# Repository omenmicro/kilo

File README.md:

# OMEN KILO

As-easy-as-possible, but still expandable single board computer with 6809 / 6309 CPU.

[Essential ICs on AliExpress](https://alitronik.com/omen-kilo-pack/)
[Essential ICs on eBay](https://alitronik.com/omen-kilo-pack-ebay/)

_Great thank to the [Svejda - Goldmann](https://svejda-goldmann.cz/) for the great OMEN artworks_

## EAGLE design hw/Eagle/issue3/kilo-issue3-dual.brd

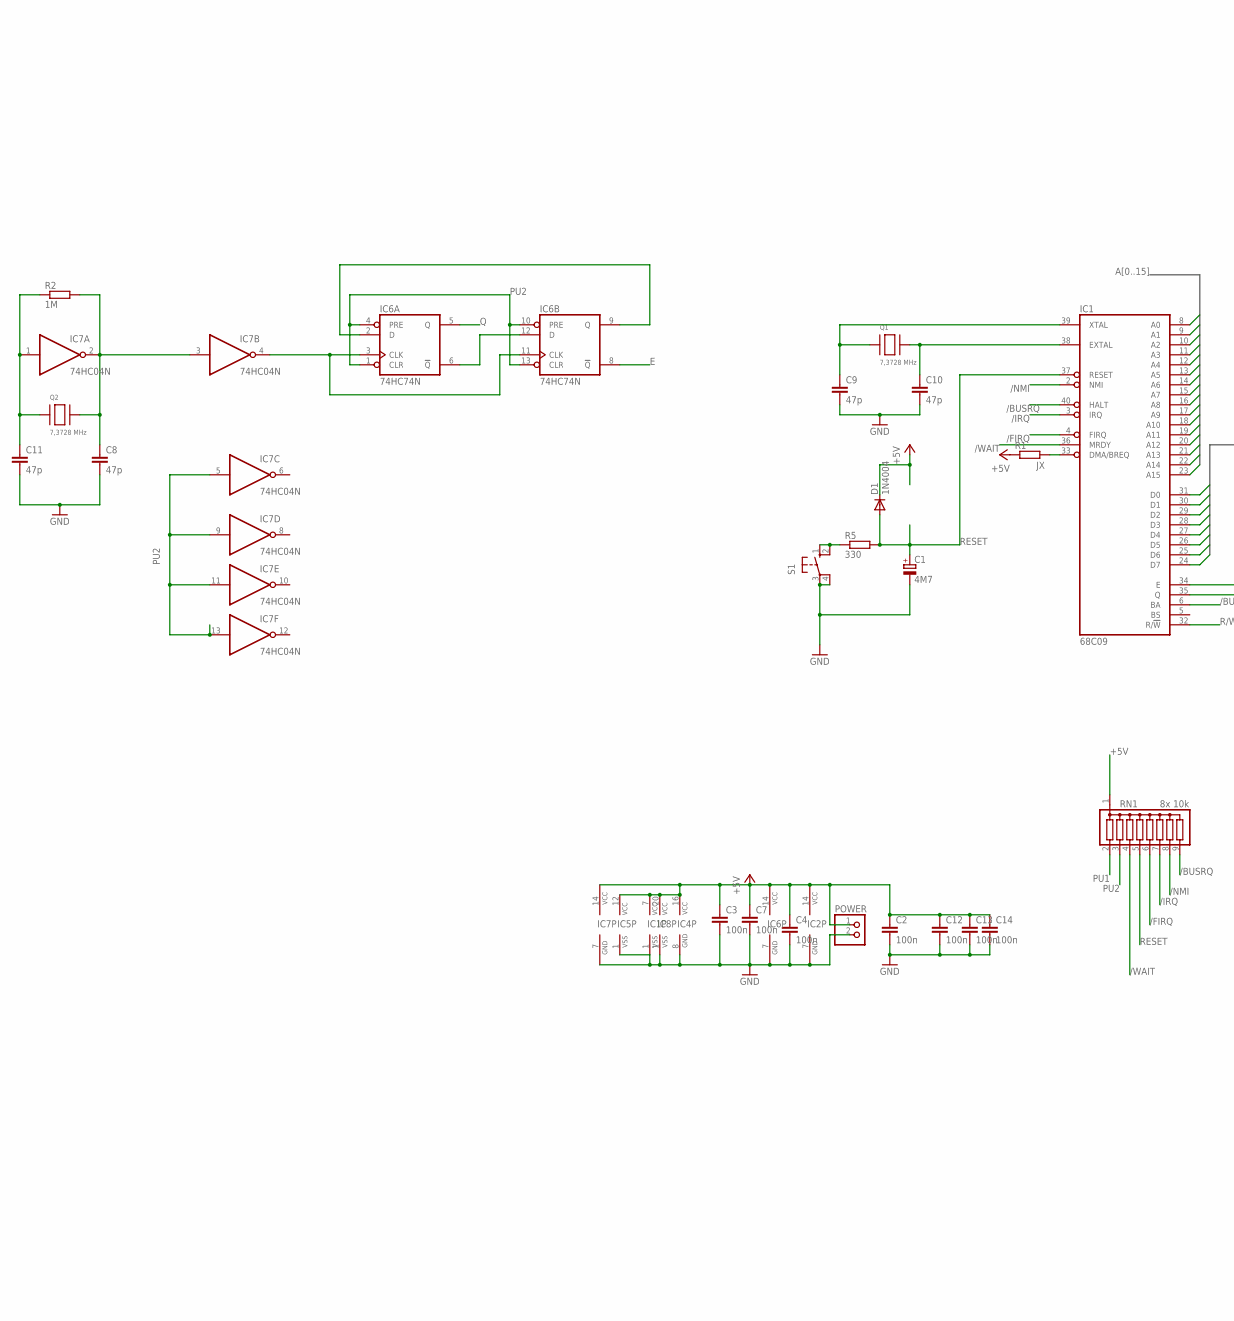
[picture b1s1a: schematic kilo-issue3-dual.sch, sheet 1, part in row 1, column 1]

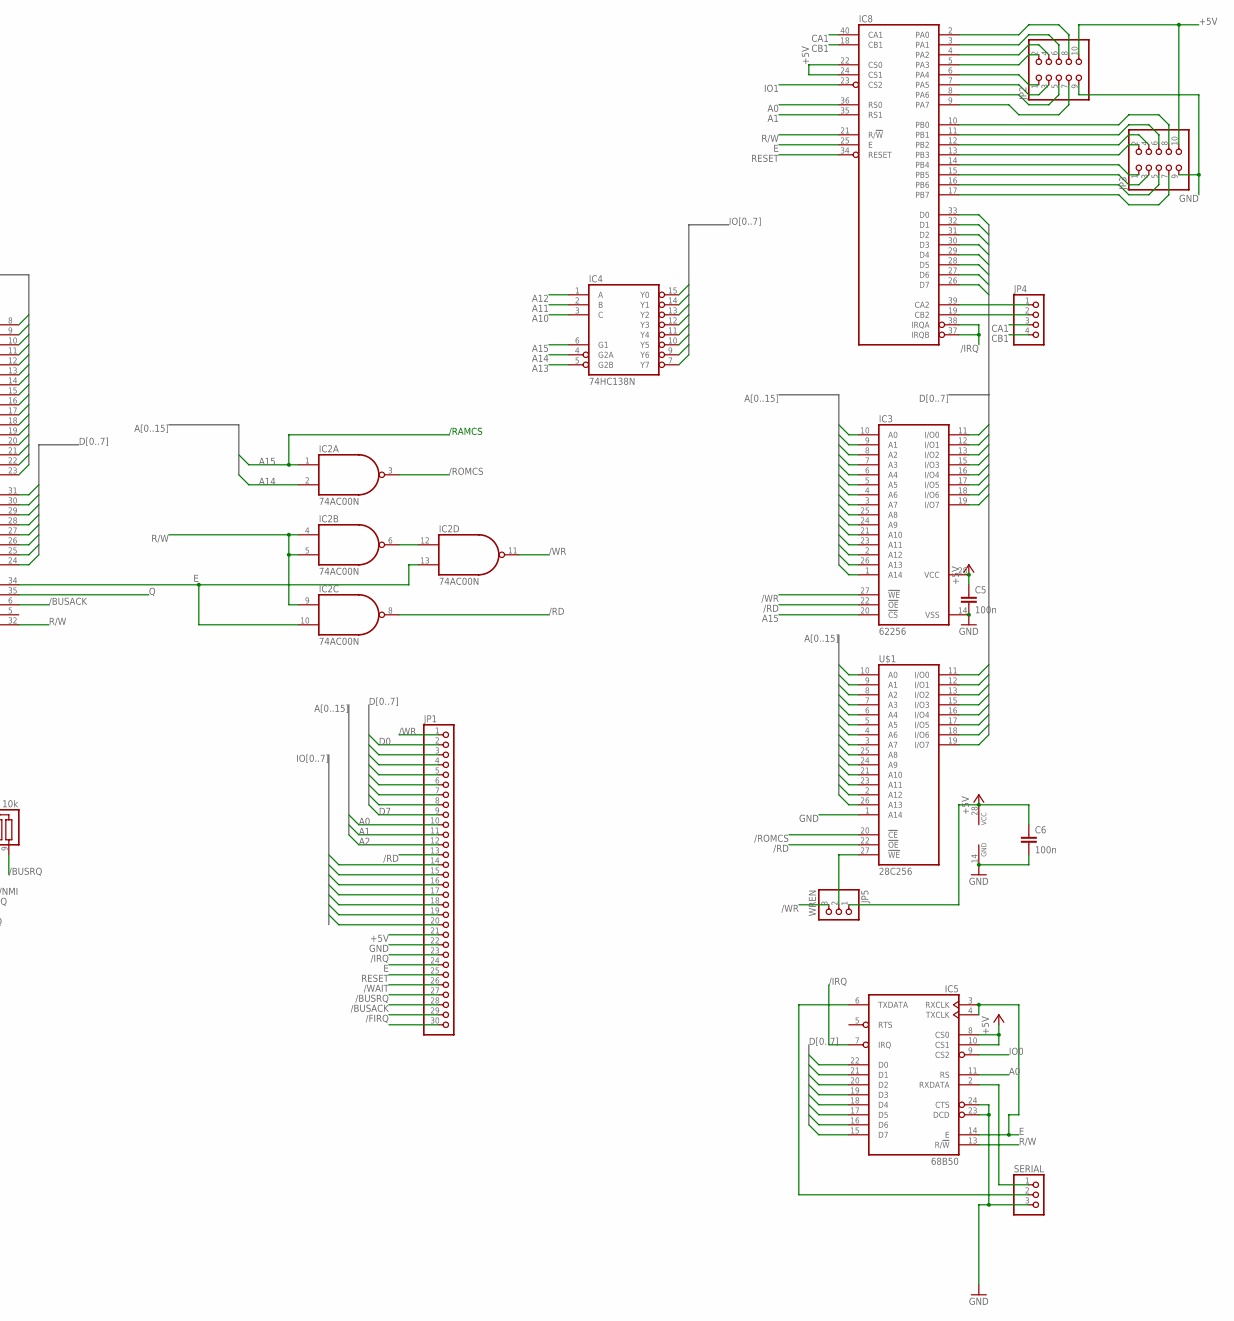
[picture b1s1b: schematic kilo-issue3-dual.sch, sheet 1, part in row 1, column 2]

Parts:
C1: 4M7; E2,5-6
C2, C3, C4, C5, C6, C7, C12, C13, C14: 100n; C025-030X050
C8, C9, C10, C11: 47p; C025-030X050
D1: 1N4004; DO41-10
IC1: 68C09; DIL40
IC2: 74AC00N; DIL14
IC3: 62256; DIL28-6
IC4: 74HC138N; DIL16
IC5: 68B50; DIL24
IC6: 74HC74N; DIL14
IC7: 74HC04N; DIL14
IC8: 6821; DIL40
JP1: PINHD-1X30; 1X30
JP2, JP3: PINHD-2X5; 2X05
JP4: PINHD-1X4; 1X04
JP5: WREN; 1X03
POWER: PINHD-1X2; 1X02
Q1, Q2: 7,3728 MHz; HC49US
R1: JX; M0805
R2: 1M; 0207/7
R5: 330; 0207/7
RN1: 8x 10k; SIL9
S1: 40-XX; B3F-40XX
SERIAL: PINHD-1X3; 1X03
U$1: 28C256; DIL28

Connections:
+5V: C2.1, C3.1, C4.1, C5.1, C6.1, C7.1, C12.1, C13.1, C14.1, D1.C, IC1.7 (VCC), IC2.14 (VCC), IC3.28 (VCC), IC4.16 (VCC), IC5.8 (CS0), IC5.10 (CS1), IC5.12 (VCC), IC6.14 (VCC), IC7.14 (VCC), IC8.20 (VCC), IC8.22 (CS0), IC8.24 (CS1), JP1.21, JP2.10, JP3.10, JP5.1, POWER.1, R1.1, RN1.1, U$1.28 (VCC)
/BUSACK: IC1.6 (BA), JP1.28
/BUSRQ: IC1.40 (HALT), JP1.27, RN1.9
/FIRQ: IC1.4 (FIRQ), JP1.29, RN1.6
/IRQ: IC1.3 (IRQ), IC5.7 (IRQ), IC8.37 (IRQB), IC8.38 (IRQA), JP1.23, RN1.7
/NMI: IC1.2 (NMI), RN1.8
/RD: IC2.8 (O), IC3.22 (!OE), JP1.13, U$1.22 (!OE)
/ROMCS: IC2.3 (O), U$1.20 (!CE)
/WAIT: IC1.36 (MRDY), JP1.26, RN1.4
/WR: IC2.11 (O), IC3.27 (!WE), JP1.1, JP5.3
A0: IC1.8 (A0), IC3.10 (A0), IC5.11 (RS), IC8.36 (RS0), JP1.10, U$1.10 (A0)
A1: IC1.9 (A1), IC3.9 (A1), IC8.35 (RS1), JP1.11, U$1.9 (A1)
A2: IC1.10 (A2), IC3.8 (A2), JP1.12, U$1.8 (A2)
A3: IC1.11 (A3), IC3.7 (A3), U$1.7 (A3)
A4: IC1.12 (A4), IC3.6 (A4), U$1.6 (A4)
A5: IC1.13 (A5), IC3.5 (A5), U$1.5 (A5)
A6: IC1.14 (A6), IC3.4 (A6), U$1.4 (A6)
A7: IC1.15 (A7), IC3.3 (A7), U$1.3 (A7)
A8: IC1.16 (A8), IC3.25 (A8), U$1.25 (A8)
A9: IC1.17 (A9), IC3.24 (A9), U$1.24 (A9)
A10: IC1.18 (A10), IC3.21 (A10), IC4.3 (C), U$1.21 (A10)
A11: IC1.19 (A11), IC3.23 (A11), IC4.2 (B), U$1.23 (A11)
A12: IC1.20 (A12), IC3.2 (A12), IC4.1 (A), U$1.2 (A12)
A13: IC1.21 (A13), IC3.26 (A13), IC4.5 (G2B), U$1.26 (A13)
A14: IC1.22 (A14), IC2.2 (I1), IC3.1 (A14), IC4.4 (G2A)
A15: IC1.23 (A15), IC2.1 (I0), IC3.20 (!CS), IC4.6 (G1)
CA1: IC8.40 (CA1), JP4.3
CB1: IC8.18 (CB1), JP4.4
D0: IC1.31 (D0), IC3.11 (I/O0), IC5.22 (D0), IC8.33 (D0), JP1.2, U$1.11 (I/O0)
D1: IC1.30 (D1), IC3.12 (I/O1), IC5.21 (D1), IC8.32 (D1), JP1.3, U$1.12 (I/O1)
D2: IC1.29 (D2), IC3.13 (I/O2), IC5.20 (D2), IC8.31 (D2), JP1.4, U$1.13 (I/O2)
D3: IC1.28 (D3), IC3.15 (I/O3), IC5.19 (D3), IC8.30 (D3), JP1.5, U$1.15 (I/O3)
D4: IC1.27 (D4), IC3.16 (I/O4), IC5.18 (D4), IC8.29 (D4), JP1.6, U$1.16 (I/O4)
D5: IC1.26 (D5), IC3.17 (I/O5), IC5.17 (D5), IC8.28 (D5), JP1.7, U$1.17 (I/O5)
D6: IC1.25 (D6), IC3.18 (I/O6), IC5.16 (D6), IC8.27 (D6), JP1.8, U$1.18 (I/O6)
D7: IC1.24 (D7), IC3.19 (I/O7), IC5.15 (D7), IC8.26 (D7), JP1.9, U$1.19 (I/O7)
E: IC1.34 (E), IC2.10 (I1), IC2.13 (I1), IC5.3 (RXCLK), IC5.4 (TXCLK), IC5.14 (E), IC6.8 (!Q), IC8.25 (E), JP1.24
GND: C1.-, C2.2, C3.2, C4.2, C5.2, C6.2, C7.2, C8.2, C9.2, C10.2, C11.2, C12.2, C13.2, C14.2, IC1.1 (VSS), IC2.7 (GND), IC3.14 (VSS), IC4.8 (GND), IC5.1 (VSS), IC5.23 (DCD), IC5.24 (CTS), IC6.7 (GND), IC7.7 (GND), IC8.1 (VSS), JP1.22, JP2.9, JP3.9, POWER.2, S1.3, S1.4 (P1), SERIAL.3, U$1.1 (A14), U$1.14 (GND)
IO0: IC4.15 (Y0), IC5.9 (CS2)
IO1: IC4.14 (Y1), IC8.23 (CS2), JP1.14
IO2: IC4.13 (Y2), JP1.15
IO3: IC4.12 (Y3), JP1.16
IO4: IC4.11 (Y4), JP1.17
IO5: IC4.10 (Y5), JP1.18
IO6: IC4.9 (Y6), JP1.19
IO7: IC4.7 (Y7), JP1.20
unnamed: R5.1, S1.1 (S), S1.2 (S1)
unnamed: IC1.33 (DMA/BREQ), R1.2
unnamed: IC6.2 (D), IC6.9 (Q)
unnamed: IC6.3 (CLK), IC6.11 (CLK), IC7.4 (O)
unnamed: IC6.6 (!Q), IC6.12 (D)
unnamed: C8.1, IC7.2 (O), IC7.3 (I), Q2.P$2, R2.2
unnamed: C11.1, IC7.1 (I), Q2.P$1, R2.1
unnamed: IC8.6 (PA4), JP2.1
unnamed: IC2.6 (O), IC2.12 (I0)
unnamed: IC8.7 (PA5), JP2.3
unnamed: IC8.8 (PA6), JP2.5
unnamed: IC8.9 (PA7), JP2.7
unnamed: IC8.5 (PA3), JP2.2
unnamed: IC8.4 (PA2), JP2.4
unnamed: IC8.3 (PA1), JP2.6
unnamed: IC8.2 (PA0), JP2.8
unnamed: IC8.13 (PB3), JP3.2
unnamed: IC8.14 (PB4), JP3.1
unnamed: IC8.12 (PB2), JP3.4
unnamed: IC8.15 (PB5), JP3.3
unnamed: IC8.11 (PB1), JP3.6
unnamed: IC8.16 (PB6), JP3.5
unnamed: IC8.17 (PB7), JP3.7
unnamed: IC8.10 (PB0), JP3.8
unnamed: IC8.39 (CA2), JP4.1
unnamed: IC8.19 (CB2), JP4.2
unnamed: JP5.2, U$1.27 (!WE)
unnamed: C10.1, IC1.38 (EXTAL), Q1.P$2
unnamed: IC5.2 (RXDATA), SERIAL.1
unnamed: IC5.6 (TXDATA), SERIAL.2
PHI0: C9.1, IC1.39 (XTAL), Q1.P$1
PU1: RN1.2
PU2: IC6.1 (CLR), IC6.4 (PRE), IC6.10 (PRE), IC6.13 (CLR), IC7.5 (I), IC7.9 (I), IC7.11 (I), IC7.13 (I), RN1.3
Q: IC1.35 (Q), IC6.5 (Q)
R/W: IC1.32 (R/!W), IC2.4 (I0), IC2.5 (I1), IC2.9 (I0), IC5.13 (R/!W), IC8.21 (R/!W)
RESET: C1.+, D1.A, IC1.37 (RESET), IC8.34 (RESET), JP1.25, R5.2, RN1.5

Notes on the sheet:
/RAMCS

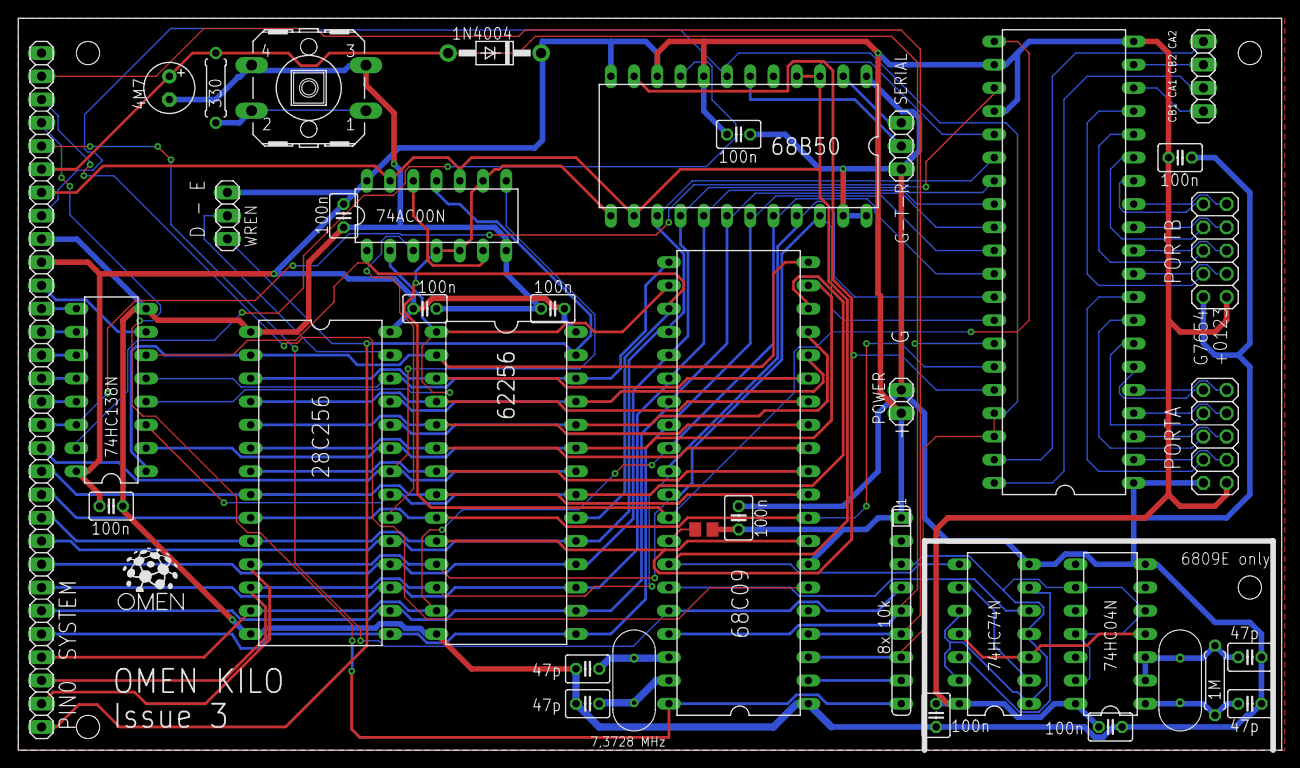
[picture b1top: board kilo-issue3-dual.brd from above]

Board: 2 copper layers, 138.1 x 80.0 mm, 38 parts (0 on the bottom side), 81 nets.

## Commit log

2018-09-30 First
2018-09-30 All in one
2018-10-07 Monitor + BASIC
2018-10-07 BRD v1 fix
2018-10-07 Issue 2
2018-11-21 HW revision 2
2018-11-21 Monitor v2
2018-12-01 Docs
2018-12-14 Issue 3
2019-03-31 packs
2019-05-19 contributions
2019-10-12 Patreon
